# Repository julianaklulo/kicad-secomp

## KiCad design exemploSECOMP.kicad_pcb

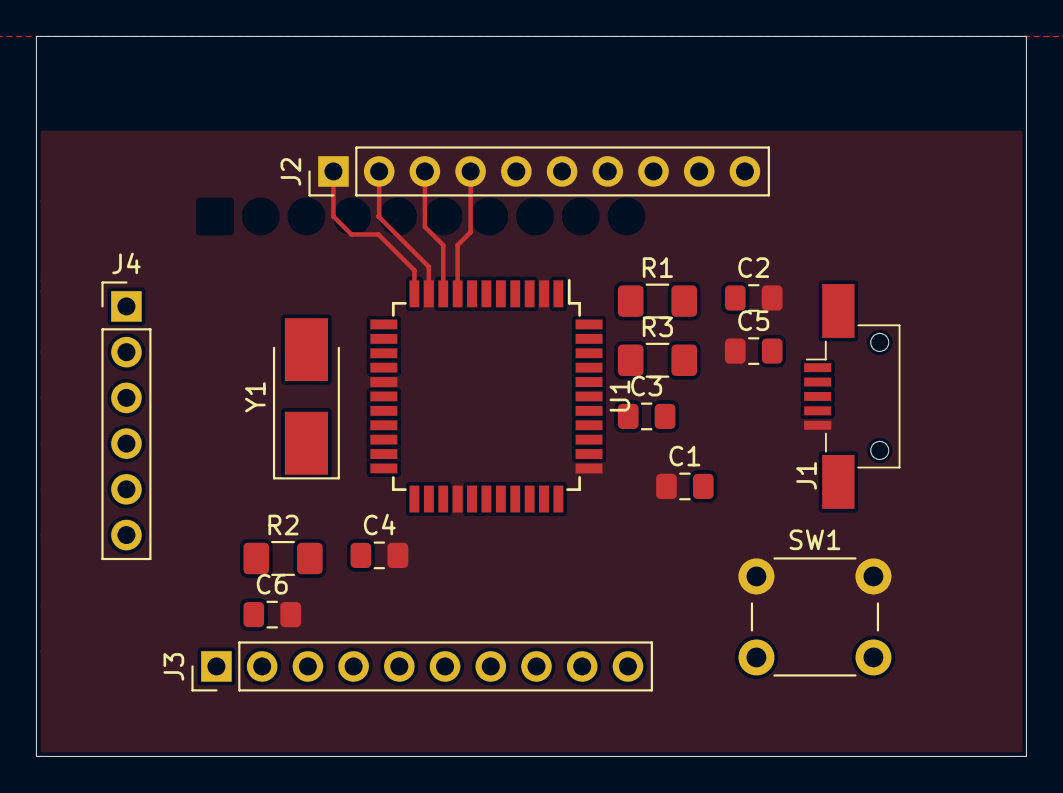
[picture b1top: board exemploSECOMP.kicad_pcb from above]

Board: 2 copper layers, 55.0 x 40.0 mm, 16 parts (0 on the bottom side), 30 nets.

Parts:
C1, C2: 15pF; C_0805_2012Metric_Pad1.15x1.40mm_HandSolder
C3: 1u; C_0805_2012Metric_Pad1.15x1.40mm_HandSolder
C4: 1uF; C_0805_2012Metric_Pad1.15x1.40mm_HandSolder
C5, C6: 100nF; C_0805_2012Metric_Pad1.15x1.40mm_HandSolder
J1: USB_B_Mini; USB_Mini-B_AdamTech_MUSB-B5-S-VT-TSMT-1_SMD_Vertical
J2, J3: Conn_01x10_Female; PinHeader_1x10_P2.54mm_Vertical
J4: Conn_01x06_Female; PinHeader_1x06_P2.54mm_Vertical
R1, R2: 22R; R_1206_3216Metric_Pad1.42x1.75mm_HandSolder
R3: 10k; R_1206_3216Metric_Pad1.42x1.75mm_HandSolder
SW1: SW_Push; SW_PUSH_6mm
U1: ATmega16U4-AU; TQFP-44_10x10mm_P0.8mm
Y1: 16MHz; Crystal_SMD_5032-2Pin_5.0x3.2mm_HandSoldering

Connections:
+5V: C4.1, C5.2, C6.1, J1.1, R3.1, U1.2, U1.7, U1.14, U1.24, U1.34, U1.44
GND: C1.1, C2.2, C4.2, C5.1, C6.2, J1.5, SW1.1, U1.5, U1.15, U1.23, U1.35, U1.43
unnamed: C1.2, U1.17, Y1.1
unnamed: C2.1, U1.16, Y1.2
unnamed: C3.2, U1.6
unnamed: J1.2, R2.2
unnamed: J1.3, R1.1
unnamed: J3.1, U1.18
unnamed: J3.2, U1.19
unnamed: J3.3, U1.20
unnamed: J3.4, U1.21
unnamed: J3.5, U1.25
unnamed: J3.6, U1.22
unnamed: J3.7, U1.26
unnamed: J3.8, U1.27
unnamed: J3.9, U1.33
unnamed: J3.10, U1.1
unnamed: J4.1, U1.41
unnamed: J4.2, U1.40
unnamed: J4.3, U1.39
unnamed: J4.4, U1.38
unnamed: J4.5, U1.37
unnamed: J4.6, U1.36
unnamed: R1.2, U1.4
unnamed: R2.1, U1.3
unnamed: R3.2, SW1.2, U1.13
Pino8: J2.4, U1.8
Pino9: J2.3, U1.9
Pino10: J2.2, U1.10
Pino11: J2.1, U1.11

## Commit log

2019-09-12 Adiciona MCU e USB
2019-09-12 Adiciona cristal, UCAP e capacitores de bypass
2019-09-12 Adiciona reset e pin headers
2019-09-12 Adiciona annotation automaticamente pela interface do KiCAD
2019-09-12 Adiciona footprints
2019-09-12 Cria PDF do esquemático
2019-09-12 Adiciona labels para não cruzar os fios
2019-09-12 Cria o layout da PCB
